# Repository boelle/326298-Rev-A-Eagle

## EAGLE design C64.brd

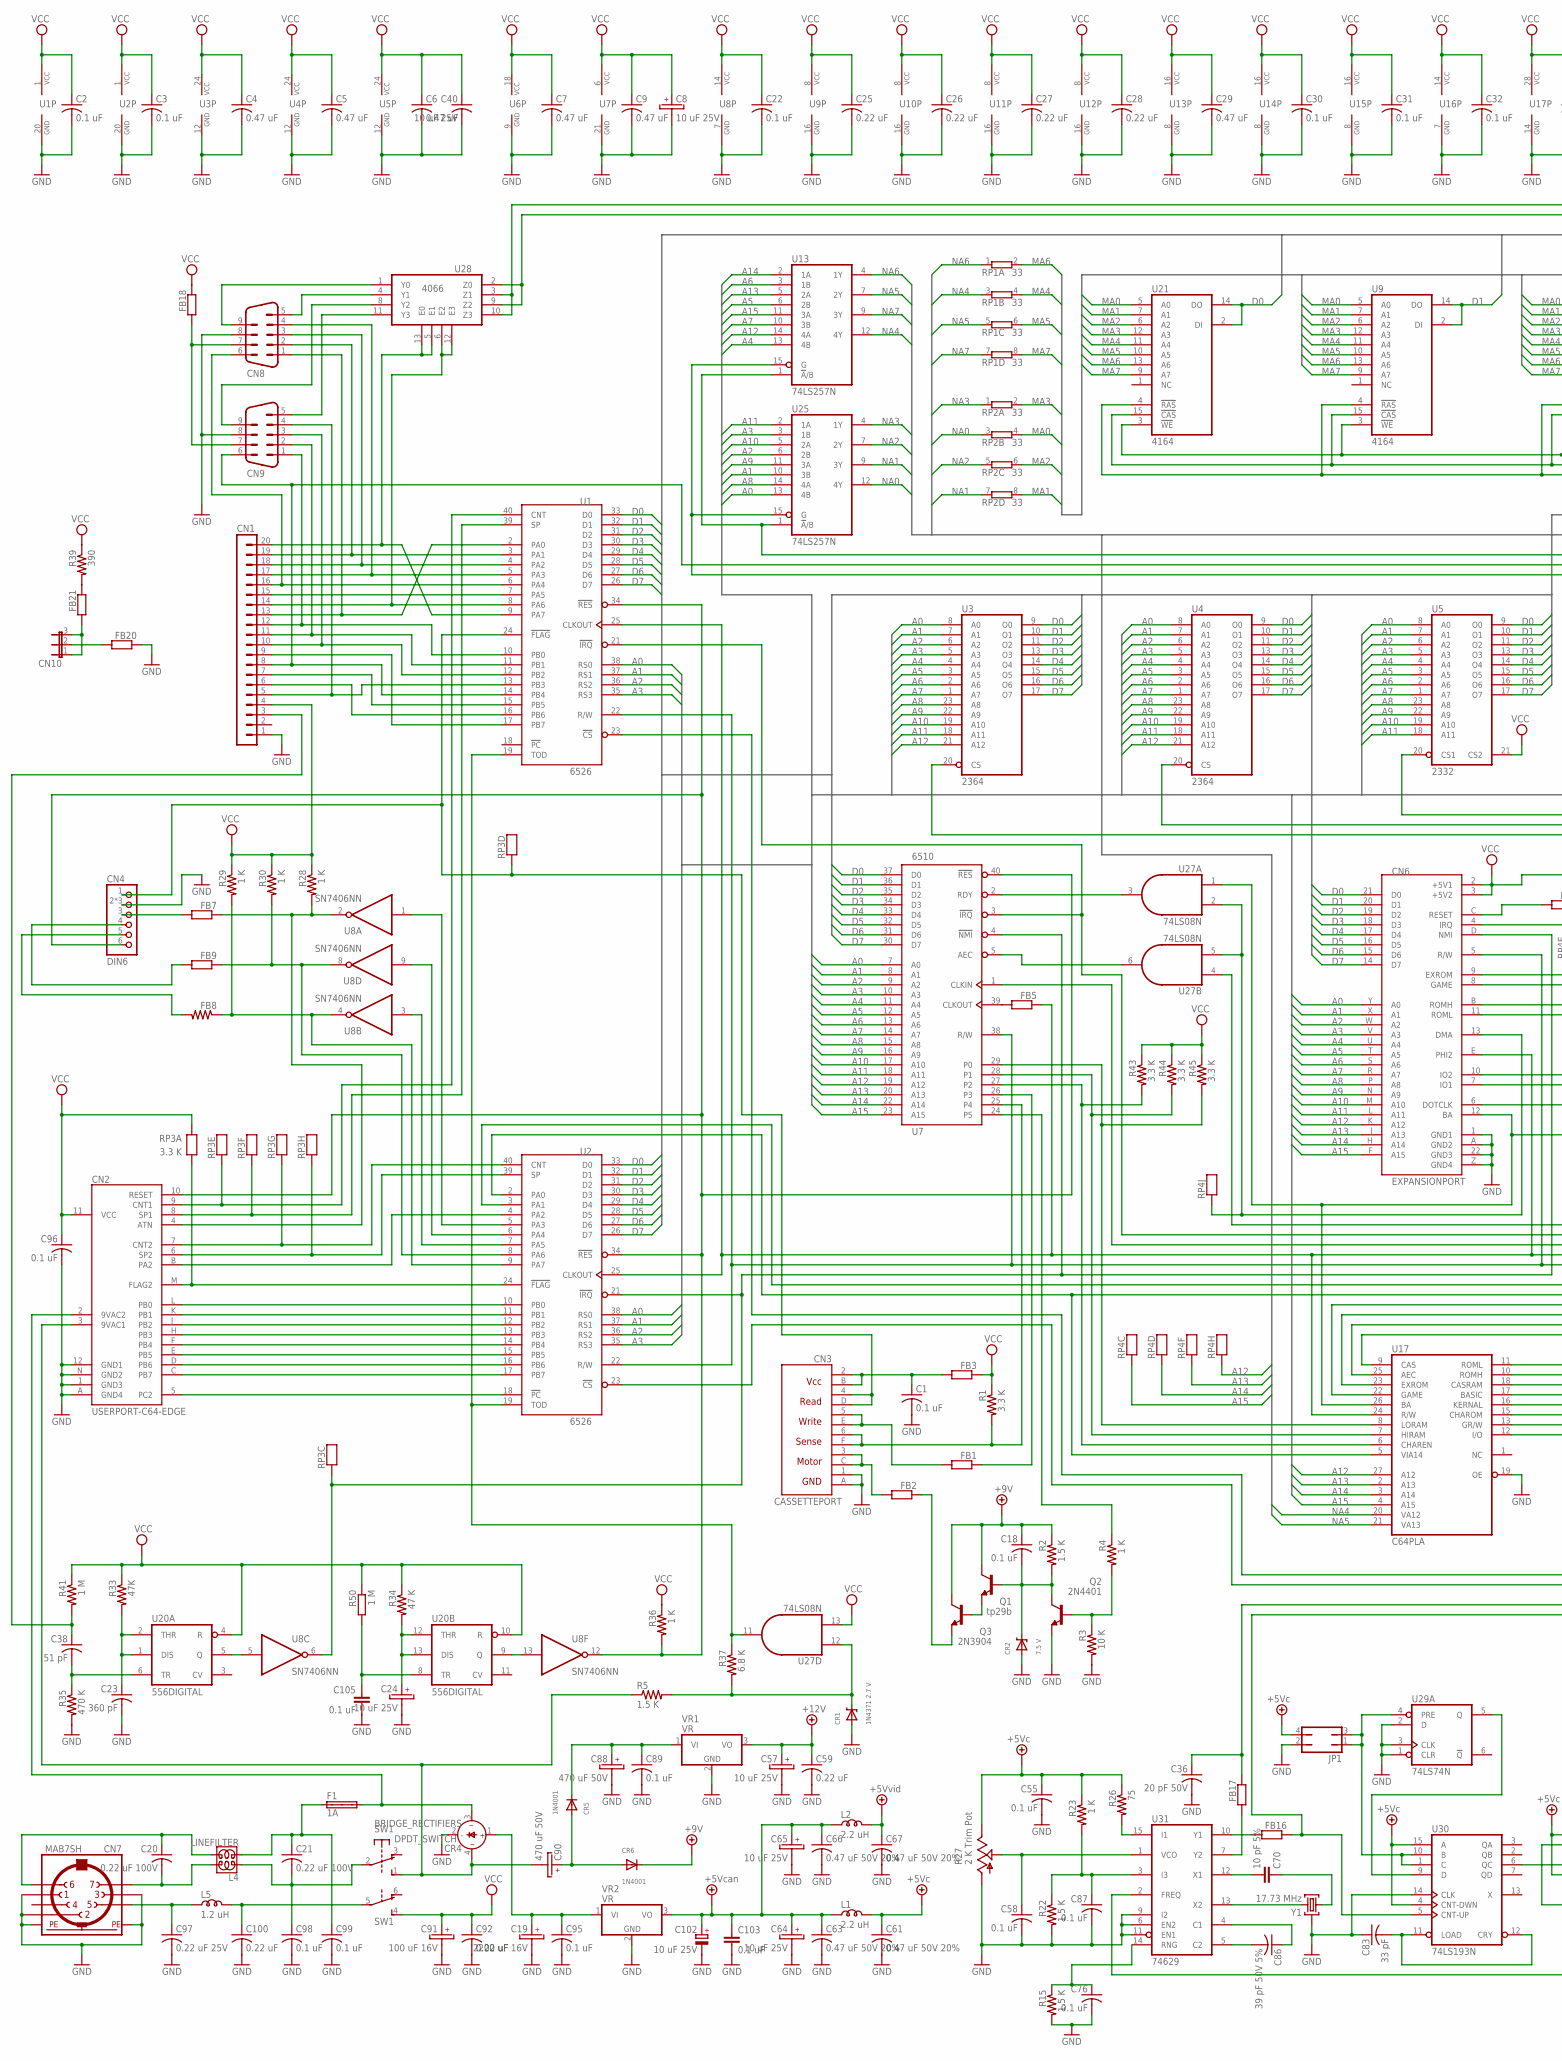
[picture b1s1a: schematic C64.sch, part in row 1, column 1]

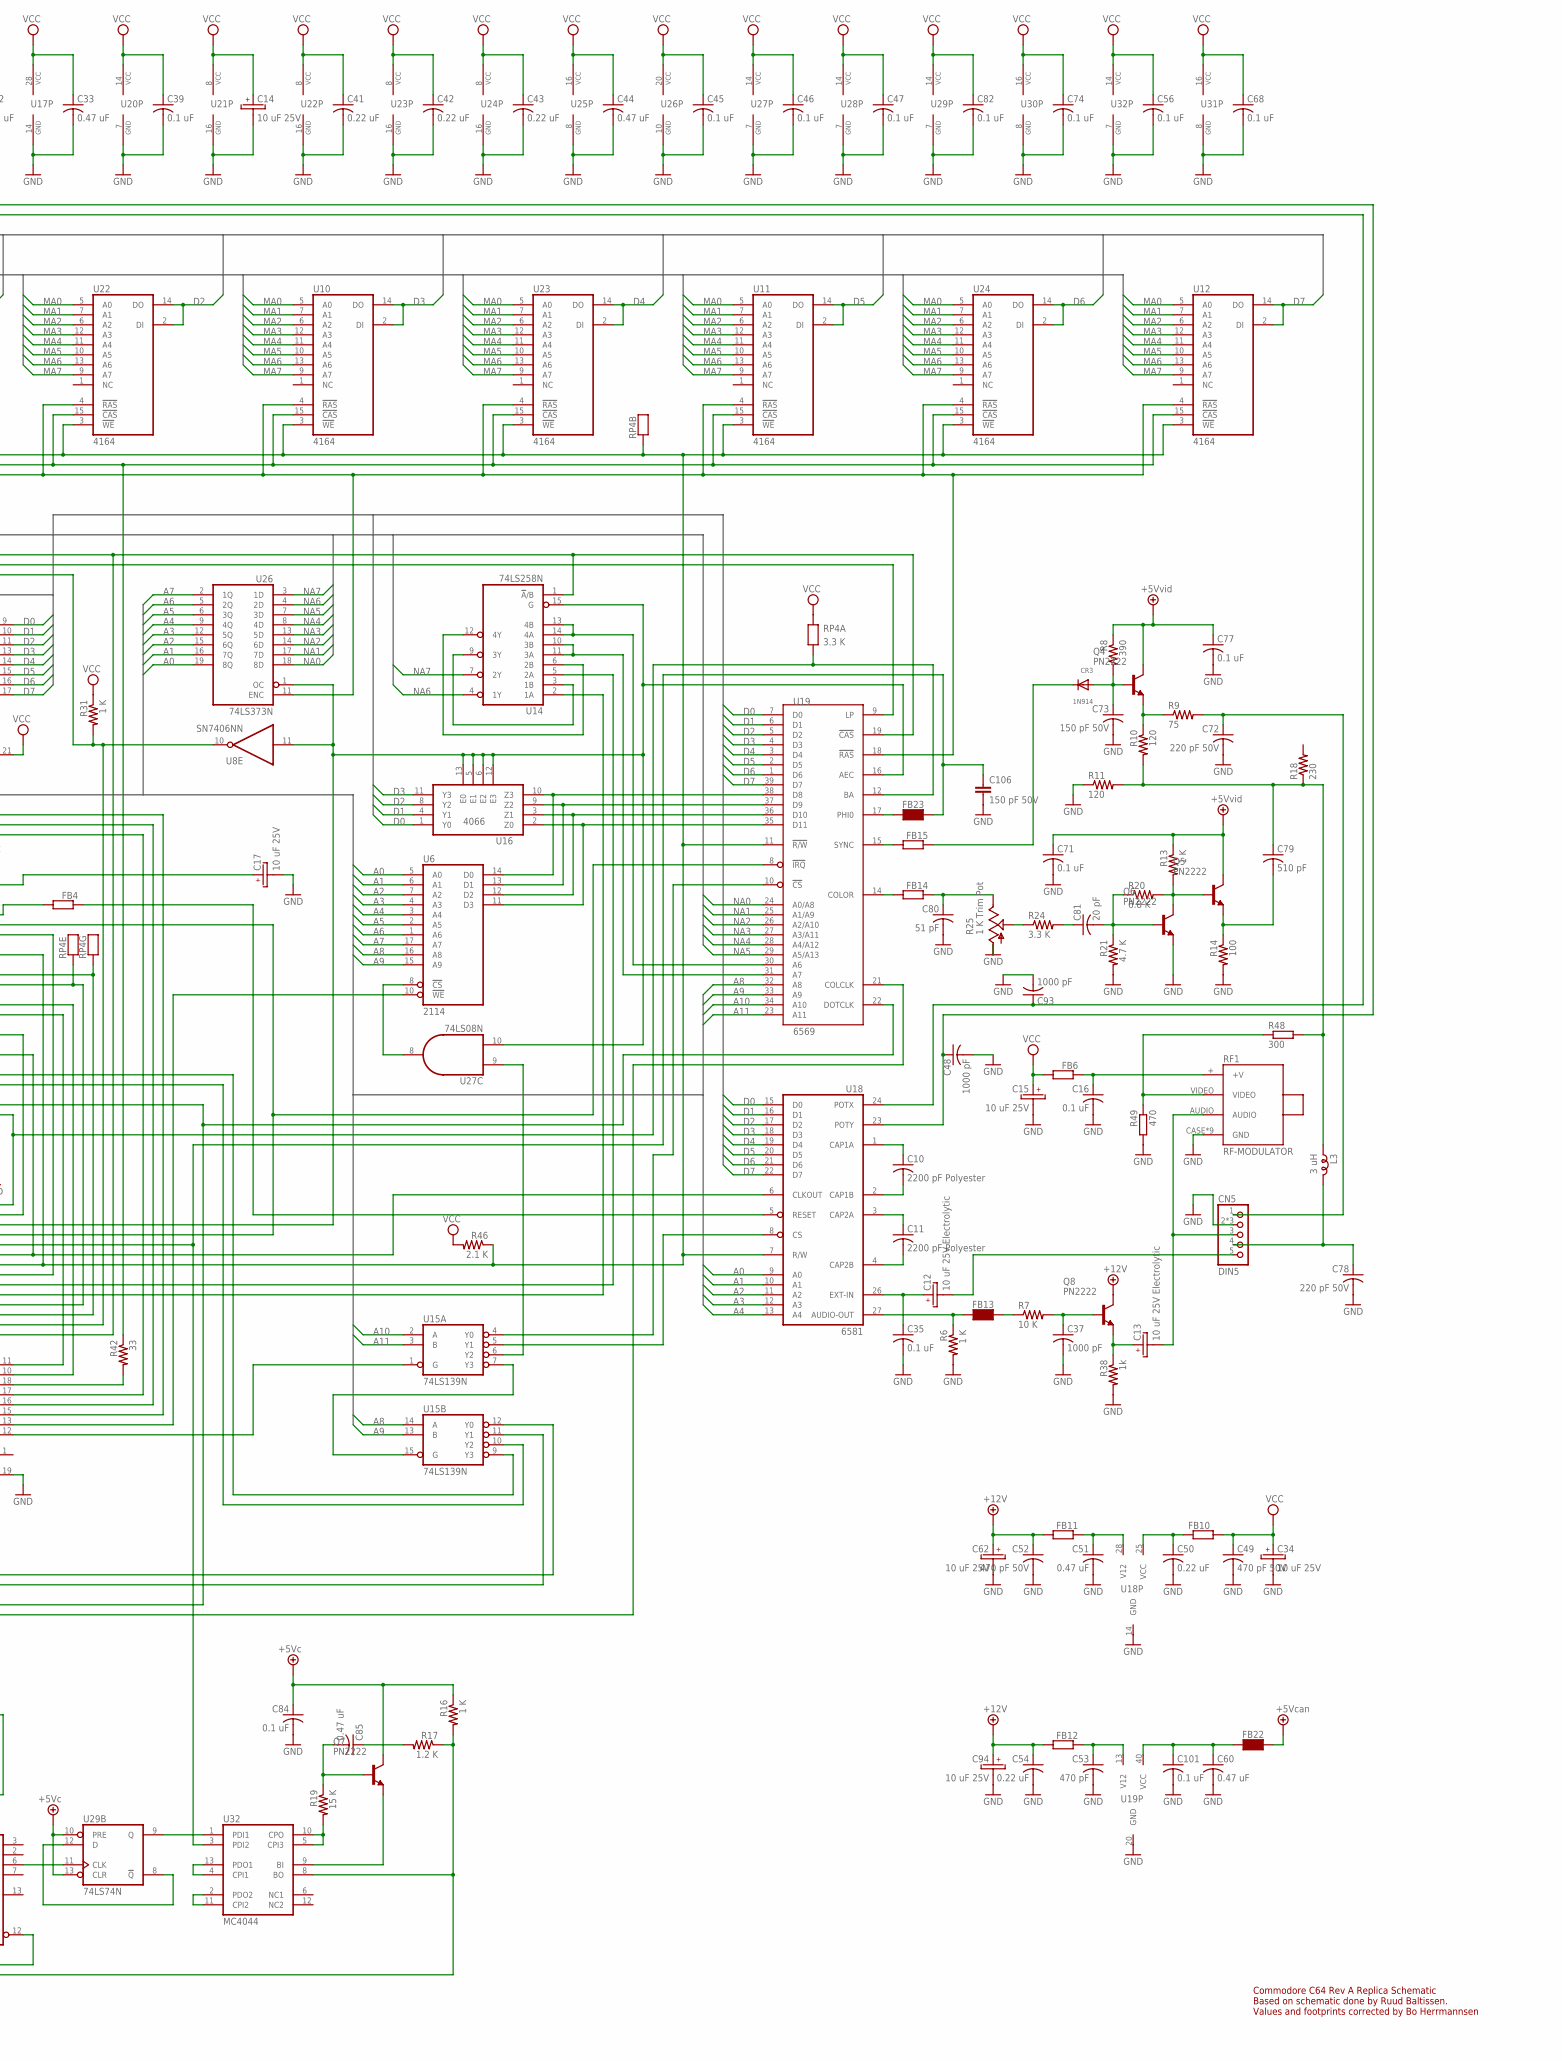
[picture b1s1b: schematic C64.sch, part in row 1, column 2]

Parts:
C1, C2, C3, C16, C18, C30, C31, C32, C35, C45, C46, C47, C89, C95, C96: 0.1 uF; 0307/12
C4, C5, C6, C7, C9, C29, C33, C44, C51: 0.47 uF; 0307/12
C8, C15, C17, C34, C57, C62, C94: 10 uF 25V; E2,5-6E
C10, C11: 2200 pF Polyester; 0307/12
C12, C13: 10 uF 25V Electrolytic; E2,5-6E
C14, C24, C64, C65: 10 uF 25V; CAPACITOR_ELECTROLYTIC_2.5_6
C19: 2200 uF 16V; E37-31.5-17.5-E
C20, C21: 0.22 uF 100V; 0203
C22, C39: 0.1 uF; 12_3_7
C23: 360 pF; 12_3_7
C25, C26, C27, C28, C41, C42, C43: 0.22 uF; 12_3_7
C36: 20 pF 50V; 12_03_07
C37, C48, C93: 1000 pF; 0307/12
C38: 51 pF; 12_3_7
C40: 10 uF 25V; 12_3_7
C49, C52: 470 pF 50V; 0307/12
C50, C54, C59, C92: 0.22 uF; 0307/12
C53: 470 pF; 0307/12
C55, C56, C58, C68, C71, C74, C76, C77, C82, C84, C87: 0.1 uF; 12_03_07
C60, C85: 0.47 uF; 12_03_07
C61, C63, C66, C67: 0.47 uF 50V 20%; 15_4_10
C70: 10 pF 5%; C075-032X103
C72, C78: 220 pF 50V; 12_03_07
C73: 150 pF 50V; 12_03_07
C79: 510 pF; 12_03_07
C80: 51 pF; 12_03_07
C81: 20 pF; 12_03_07
C83: 33 pF; 12_03_07
C86: 39 pF 50V 5%; 12_03_07
C88, C90: 470 uF 50V; E37-31.5-17.5-E
C91: 100 uF 16V; C_E_5-9
C97: 0.22 uF 25V; 0203
C98, C99: 0.1 uF; 0203
C100: 0.22 uF; 0203
C101: 0.1 uF; 6_03_8.5
C102: 10 uF 25V; E3,5-10
C103, C105: 0.1 uF; C075-032X103
C106: 150 pF 50V; C075-032X103
CN1: MA20-1
CN2: USERPORT-C64-EDGE; UPS24EDGE
CN3: CASSETTEPORT
CN4: DIN6
CN5: DIN5
CN6: EXPANSIONPORT
CN7: MAB7SH
CN8, CN9: CONTROL_PORT
CN10: JP2E; JP2
CR1: 1N4371 2.7 V; D_0307/12
CR2: 7.5 V; D_0307/12
CR3: 1N914; D_0307/12
CR4: BRIDGE_RECTIFIERS; DIL4
CR5, CR6: 1N4001; D_0307/12
F1: 1A; SH32
FB1, FB2, FB3, FB4, FB5, FB6, FB10, FB11, FB12, FB14, FB15, FB16, FB17, FB18, FB20, FB21: FB_0307/12R_0307/12; 12_03_07
FB7, FB9: FERRITE_BEAD_12_3_7R_0307/12; 12_3_7
FB8: RESISTOR_12_3_7R_0307/12; 12_3_7
FB13, FB22, FB23: FERRIT; R5
JP1: JP2Q
L1, L2: 2.2 uH; 12_3_7
L3: 3 uH; 12_3_7
L4: LINEFILTER
L5: 1.2 uH; R5
Q1: tp29b; TO220V
Q2: 2N4401; TO92
Q3: 2N3904; TO92
Q4, Q5, Q6, Q7, Q8: PN2222; TO92
R1, R43, R44, R45: 3.3 K; 0307/12
R2, R5: 1.5 K; 0307/12
R3, R7: 10 K; 0307/12
R4, R6: 1 K; 0307/12
R8: 390; 12_03_07
R9, R26: 75; 12_03_07
R10, R11: 120; 12_03_07
R13, R16, R23: 1 K; 12_03_07
R14: 100; 12_03_07
R15, R22: 1.5 K; 12_03_07
R17: 1.2 K; 12_03_07
R18: 230; 12_03_07
R19: 15 K; 12_03_07
R20: 6.8 K; 12_03_07
R21: 4.7 K; 12_03_07
R24: 3.3 K; 12_03_07
R25: 1 K Trim Pot; POT_METER
R27: 2 K Trim Pot; POT_METER
R28, R29, R30, R31, R36: 1 K; 12_3_7
R33: 47K; 12_3_7
R34: 47 K; 12_3_7
R35: 470 K; 12_3_7
R37: 6.8 K; 0307/12
R38: 1k; 12_3_7
R39: 390; 0307/12
R41: 1 M; 0307/12
R42: 33; 12_3_7
R46: 2.1 K; 0307/12
R48: 300; 0204V
R49: 470; 0204V
R50: 1 M; 0204V
RF1: RF-MODULATOR
RP1, RP2: 33; RESISTOR_PACK_4
RP3: 3.3 K; RP8
RP4: 3.3 K; RP9
SW1: DPDT_SWITCH
U1, U2: 6526; DIP40
U3, U4: 2364; DIL24
U5: 2332; DIL24
U6: 2114; DIL18
U7: 6510; DIP40
U8: SN7406NN; DIL14
U9, U10, U11, U12, U21, U22, U23, U24: 4164; DIL16
U13, U25: 74LS257N; DIL16@1
U14: 74LS258N; DIL16@1
U15: 74LS139N; DIL16@1
U16, U28: 4066; DIL14@1
U17: C64PLA; DIL28
U18: 6581; DIL28
U19: 6569; DIP40
U20: 556DIGITAL; DIL14
U26: 74LS373N; DIL20
U27: 74LS08N; DIL14@1
U29: 74LS74N; DIL14@1
U30: 74LS193N; DIL16@1
U31: 74629; DIL16@1
U32: MC4044; DIL14@1
VR1, VR2: VR; TO220V
Y1: 17.73 MHz; HC49TL-H

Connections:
+5V: C63.1, C64.+ (1), C65.+ (1), C66.1, C102.+, C103.1, FB22.2, L1.1, L2.1, VR2.3 (VO)
+5V/1: C67.1, C71.1, C77.1, L2.2, Q4.1 (C), Q5.1 (C), R8.1, R13.1
+5V/2: C55.1, C61.1, C84.1, JP1.4, L1.2, Q7.1 (C), R16.1, R23.1, R26.1, R27.E, U29.10 (PRE), U29.13 (CLR), U30.4 (CNT-DWN), U30.15 (A)
+9V: C18.1, CR6.2 (C), Q1.2 (C), Q3.3 (C), R2.1
+12V: C52.1, C54.1, C57.+ (1), C59.1, C62.+ (1), C94.+ (1), FB11.2, FB12.2, Q8.1 (C), VR1.3 (VO)
A0: CN6.Y (A0), U1.38 (RS0), U2.38 (RS0), U3.8 (A0), U4.8 (A0), U5.8 (A0), U6.5 (A0), U7.7 (A0), U18.9 (A0), U25.13 (4B), U26.19 (8Q)
A1: CN6.X (A1), U1.37 (RS1), U2.37 (RS1), U3.7 (A1), U4.7 (A1), U5.7 (A1), U6.6 (A1), U7.8 (A1), U18.10 (A1), U25.10 (3B), U26.16 (7Q)
A2: CN6.W (A2), U1.36 (RS2), U2.36 (RS2), U3.6 (A2), U4.6 (A2), U5.6 (A2), U6.7 (A2), U7.9 (A2), U18.11 (A2), U25.6 (2B), U26.15 (6Q)
A3: CN6.V (A3), U1.35 (RS3), U2.35 (RS3), U3.5 (A3), U4.5 (A3), U5.5 (A3), U6.4 (A3), U7.10 (A3), U18.12 (A3), U25.3 (1B), U26.12 (5Q)
A4: CN6.U (A4), U3.4 (A4), U4.4 (A4), U5.4 (A4), U6.3 (A4), U7.11 (A4), U13.13 (4B), U18.13 (A4), U26.9 (4Q)
A5: CN6.T (A5), U3.3 (A5), U4.3 (A5), U5.3 (A5), U6.2 (A5), U7.12 (A5), U13.6 (2B), U26.6 (3Q)
A6: CN6.S (A6), U3.2 (A6), U4.2 (A6), U5.2 (A6), U6.1 (A6), U7.13 (A6), U13.3 (1B), U26.5 (2Q)
A7: CN6.R (A7), U3.1 (A7), U4.1 (A7), U5.1 (A7), U6.17 (A7), U7.14 (A7), U13.10 (3B), U26.2 (1Q)
A8: CN6.P (A8), U3.23 (A8), U4.23 (A8), U5.23 (A8), U6.16 (A8), U7.15 (A8), U15.14 (A), U19.32 (A8), U25.14 (4A)
A9: CN6.N (A9), U3.22 (A9), U4.22 (A9), U5.22 (A9), U6.15 (A9), U7.16 (A9), U15.13 (B), U19.33 (A9), U25.11 (3A)
A10: CN6.M (A10), U3.19 (A10), U4.19 (A10), U5.19 (A10), U7.17 (A10), U15.2 (A), U19.34 (A10), U25.5 (2A)
A11: CN6.L (A11), U3.18 (A11), U4.18 (A11), U5.18 (A11), U7.18 (A11), U15.3 (B), U19.23 (A11), U25.2 (1A)
A12: CN6.K (A12), RP4.9 (X), U3.21 (A12), U4.21 (A12), U7.19 (A12), U13.14 (4A), U17.27 (A12)
A13: CN6.J (A13), RP4.7 (X), U7.20 (A13), U13.5 (2A), U17.2 (A13)
A14: CN6.H (A14), RP4.5 (X), U7.22 (A14), U13.2 (1A), U17.3 (A14)
A15: CN6.F (A15), RP4.4 (X), U7.23 (A15), U13.11 (3A), U17.4 (A15)
D0: CN6.21 (D0), U1.33 (D0), U2.33 (D0), U3.9 (O0), U4.9 (O0), U5.9 (O0), U7.37 (D0), U16.1 (Y0), U18.15 (D0), U19.7 (D0), U21.2 (DI), U21.14 (DO)
D1: CN6.20 (D1), U1.32 (D1), U2.32 (D1), U3.10 (O1), U4.10 (O1), U5.10 (O1), U7.36 (D1), U9.2 (DI), U9.14 (DO), U16.4 (Y1), U18.16 (D1), U19.6 (D1)
D2: CN6.19 (D2), U1.31 (D2), U2.31 (D2), U3.11 (O2), U4.11 (O2), U5.11 (O2), U7.35 (D2), U16.8 (Y2), U18.17 (D2), U19.5 (D2), U22.2 (DI), U22.14 (DO)
D3: CN6.18 (D3), U1.30 (D3), U2.30 (D3), U3.13 (O3), U4.13 (O3), U5.13 (O3), U7.34 (D3), U10.2 (DI), U10.14 (DO), U16.11 (Y3), U18.18 (D3), U19.4 (D3)
D4: CN6.17 (D4), U1.29 (D4), U2.29 (D4), U3.14 (O4), U4.14 (O4), U5.14 (O4), U7.33 (D4), U18.19 (D4), U19.3 (D4), U23.2 (DI), U23.14 (DO)
D5: CN6.16 (D5), U1.28 (D5), U2.28 (D5), U3.15 (O5), U4.15 (O5), U5.15 (O5), U7.32 (D5), U11.2 (DI), U11.14 (DO), U18.20 (D5), U19.2 (D5)
D6: CN6.15 (D6), U1.27 (D6), U2.27 (D6), U3.16 (O6), U4.16 (O6), U5.16 (O6), U7.31 (D6), U18.21 (D6), U19.1 (D6), U24.2 (DI), U24.14 (DO)
D7: CN6.14 (D7), U1.26 (D7), U2.26 (D7), U3.17 (O7), U4.17 (O7), U5.17 (O7), U7.30 (D7), U12.2 (DI), U12.14 (DO), U18.22 (D7), U19.39 (D7)
GND: C1.2, C2.2, C3.2, C4.2, C5.2, C6.2, C7.2, C8.- (2), C9.2, C14.- (2), C15.- (2), C16.2, C17.- (2), C19.- (2), C22.2, C23.2, C24.- (2), C25.2, C26.2, C27.2, C28.2, C29.2, C30.2, C31.2, C32.2, C33.2, C34.- (2), C35.2, C36.2, C37.2, C39.2, C40.2, C41.2, C42.2, C43.2, C44.2, C45.2, C46.2, C47.2, C48.2, C49.2, C50.2, C51.2, C52.2, C53.2, C54.2, C55.2, C56.2, C57.- (2), C58.2, C59.2, C60.2, C61.2, C62.- (2), C63.2, C64.- (2), C65.- (2), C66.2, C67.2, C68.2, C71.2, C72.2, C73.2, C74.2, C76.2, C77.2, C78.2, C80.2, C82.2, C83.1, C84.2, C87.2, C88.- (2), C89.2, C91.- (2), C92.2, C93.2, C94.- (2), C95.2, C96.2, C97.2, C98.2, C99.2, C100.2, C101.2, C102.-, C103.2, C105.2, C106.2, CN1.1, CN2.1 (GND3), CN2.12 (GND1), CN2.A (GND4), CN2.N (GND2), CN3.1 (GND1), CN3.A (GND2), CN4.2, CN4.PE (2), CN4.PE@ (2), CN5.2, CN5.PE (2), CN5.PE@ (2), CN6.1 (GND1), CN6.22 (GND3), CN6.A (GND2), CN6.Z (GND4), CN7.1, CN7.2, CN7.3, CN7.PE, CN7.PE@ (PE), CN8.8, CN9.8, CR1.1 (A), CR2.1 (A), CR4.2 (-), FB20.1, JP1.2, Q2.1 (E), Q6.3 (E), R3.2, R6.2, R11.1, R14.2, R15.2, R21.2, R22.2, R25.A, R27.A, R35.2, R38.2, R49.2, RF1.CASE (GND), RF1.P$1 (GND), RF1.P$2 (GND), RF1.P$3 (GND), RF1.P$4 (GND), RF1.P$5 (GND), RF1.P$6 (GND), RF1.P$7 (GND), RF1.P$8 (GND), U1.20 (GND), U2.20 (GND), U3.12 (GND), U4.12 (GND), U5.12 (GND), U6.9 (GND), U7.21 (GND), U8.7 (GND), U9.16 (GND), U10.16 (GND), U11.16 (GND), U12.16 (GND), U13.8 (GND), U14.8 (GND), U15.8 (GND), U16.7 (GND), U17.14 (GND), U17.19 (OE), U18.14 (GND), U19.20 (GND), U20.7 (GND), U21.16 (GND), U22.16 (GND), U23.16 (GND), U24.16 (GND), U25.8 (GND), U26.10 (GND), U27.7 (GND), U28.7 (GND), U29.1 (CLR), U29.2 (D), U29.3 (CLK), U29.7 (GND), U30.8 (GND), U30.14 (CLK), U31.6 (EN2), U31.8 (GND), U31.9 (I2), U31.11 (EN1), U32.7 (GND), VR1.2 (GND), VR2.2 (GND), Y1.3
IRQ: CN6.4 (IRQ), U1.21 (!IRQ!), U7.3 (!IRQ!), U19.8 (!IRQ!)
MA0: RP2.4 (2), U9.5 (A0), U10.5 (A0), U11.5 (A0), U12.5 (A0), U21.5 (A0), U22.5 (A0), U23.5 (A0), U24.5 (A0)
MA1: RP2.8 (2), U9.7 (A1), U10.7 (A1), U11.7 (A1), U12.7 (A1), U21.7 (A1), U22.7 (A1), U23.7 (A1), U24.7 (A1)
MA2: RP2.6 (2), U9.6 (A2), U10.6 (A2), U11.6 (A2), U12.6 (A2), U21.6 (A2), U22.6 (A2), U23.6 (A2), U24.6 (A2)
MA3: RP2.2, U9.12 (A3), U10.12 (A3), U11.12 (A3), U12.12 (A3), U21.12 (A3), U22.12 (A3), U23.12 (A3), U24.12 (A3)
MA4: RP1.4 (2), U9.11 (A4), U10.11 (A4), U11.11 (A4), U12.11 (A4), U21.11 (A4), U22.11 (A4), U23.11 (A4), U24.11 (A4)
MA5: RP1.6 (2), U9.10 (A5), U10.10 (A5), U11.10 (A5), U12.10 (A5), U21.10 (A5), U22.10 (A5), U23.10 (A5), U24.10 (A5)
MA6: RP1.2, U9.13 (A6), U10.13 (A6), U11.13 (A6), U12.13 (A6), U21.13 (A6), U22.13 (A6), U23.13 (A6), U24.13 (A6)
MA7: RP1.8 (2), U9.9 (A7), U10.9 (A7), U11.9 (A7), U12.9 (A7), U21.9 (A7), U22.9 (A7), U23.9 (A7), U24.9 (A7)
unnamed: C12.+ (1), C35.1, U18.26 (EXT-IN)
unnamed: FB13.1, R6.1, U18.27 (AUDIO-OUT)
unnamed: FB13.2, R7.1
unnamed: C37.1, Q8.2 (B), R7.2
unnamed: C13.+ (1), Q8.3 (E), R38.1
unnamed: C10.2, U18.2 (CAP1B)
unnamed: C11.2, U18.4 (CAP2B)
unnamed: C10.1, U18.1 (CAP1A)
unnamed: C11.1, U18.3 (CAP2A)
unnamed: C13.- (2), CN5.3, RF1.AUDIO
unnamed: C12.- (2), CN5.5
unnamed: C50.1, FB10.1, U18.25 (VCC)
unnamed: C16.1, FB6.1, RF1.+ (+V)
unnamed: C51.1, FB11.1, U18.28 (V12)
unnamed: C80.1, FB14.1, R25.E
unnamed: FB14.2, U19.14 (COLOR)
unnamed: C97.1, CN7.5, L5.1
unnamed: C100.1, L5.2, SW1.5
unnamed: C20.2, CN7.7, L4.4
unnamed: C20.1, CN7.6, L4.3
unnamed: C21.1, C99.1, F1.1A, L4.2
unnamed: C21.2, C98.1, L4.1, SW1.2
unnamed: CN2.2 (9VAC2), CR4.3 (AC1), F1.2A
unnamed: C90.- (2), CN2.3 (9VAC1), CR4.4 (AC2), R5.1, SW1.1 (S)
unnamed: C19.+ (1), C95.1, CR4.1 (+), VR2.1 (VI)
unnamed: C90.+ (1), CR5.1 (A), CR6.1 (A)
unnamed: C88.+ (1), C89.1, CR5.2 (C), VR1.1 (VI)
unnamed: R24.1, R25.S
unnamed: C81.1, R24.2
unnamed: C81.2, Q6.2 (B), R20.1, R21.1
unnamed: Q5.2 (B), Q6.1 (C), R13.2, R20.2
unnamed: C79.2, Q5.3 (E), R14.1
unnamed: C79.1, L3.1, R10.2, R11.2, R18.1, R48.2
unnamed: C60.1, C101.1, FB22.1, U19.40 (VCC)
unnamed: C53.1, FB12.1, U19.13 (V12)
unnamed: C73.1, CR3.1 (A), Q4.2 (B), R8.2
unnamed: CR3.2 (C), FB15.1
unnamed: Q4.3 (E), R9.1, R10.1
unnamed: C72.1, CN5.1, R9.2
unnamed: FB15.2, U19.15 (SYNC)
unnamed: C78.1, CN5.4, L3.2
unnamed: U14.10 (3B), U14.11 (3A), U19.31 (A7)
unnamed: R48.1, R49.1, RF1.VIDEO
unnamed: U14.13 (4B), U14.14 (4A), U19.30 (A6)
unnamed: U14.3 (1B), U14.9 (3Y)
unnamed: U14.6 (2B), U14.12 (4Y)
unnamed: U6.14 (D0), U16.10 (Z3), U19.38 (D8)
unnamed: U6.13 (D1), U16.9 (Z2), U19.37 (D9)
unnamed: U6.12 (D2), U16.3 (Z1), U19.36 (D10)
unnamed: U6.11 (D3), U16.2 (Z0), U19.35 (D11)
unnamed: R42.2, U17.18 (CASRAM)
unnamed: U8.11 (I), U14.15 (G), U16.5 (E1), U16.6 (E2), U16.12 (E3), U16.13 (E0), U19.16 (AEC), U26.1 (OC), U27.4 (I0), U27.10 (I1)
unnamed: U13.1 (!A!/B), U14.1 (!A!/B), U17.9 (CAS), U19.19 (!CAS!), U25.1 (!A!/B)
unnamed: R42.1, U9.15 (!CAS), U10.15 (!CAS), U11.15 (!CAS), U12.15 (!CAS), U21.15 (!CAS), U22.15 (!CAS), U23.15 (!CAS), U24.15 (!CAS)
unnamed: U9.4 (!RAS), U10.4 (!RAS), U11.4 (!RAS), U12.4 (!RAS), U19.18 (!RAS!), U21.4 (!RAS), U22.4 (!RAS), U23.4 (!RAS), U24.4 (!RAS), U26.11 (ENC)
unnamed: U6.8 (!CS), U27.8 (O)
unnamed: U8.13 (I), U20.9 (Q)
unnamed: C24.+ (1), R34.2, U20.12 (THR), U20.13 (DIS)
unnamed: C105.1, R50.2, U20.8 (TR)
unnamed: U8.5 (I), U20.5 (Q)
unnamed: C23.1, R33.2, U20.1 (DIS), U20.2 (THR)
unnamed: C38.2, R35.1, U20.6 (TR)
unnamed: C38.1, CN1.3, R41.2
unnamed: R26.2, U31.15 (I1)
unnamed: C58.1, R27.S, U31.1 (VCO)
unnamed: FB16.2, U31.10 (Y1)
unnamed: U31.13 (X2), Y1.2
unnamed: C70.2, U31.12 (X1)
unnamed: C70.1, Y1.1
unnamed: FB16.1, U19.21 (COLCLK), U30.5 (CNT-UP)
unnamed: C83.2, U30.11 (LOAD), U30.12 (CRY)
unnamed: JP1.1, JP1.3, U29.4 (PRE), U30.1 (C), U30.10 (B)
unnamed: U29.5 (Q), U30.9 (D)
unnamed: R16.2, R17.1, U31.2 (FREQ), U32.8 (BO)
unnamed: U29.11 (CLK), U30.6 (QC)
unnamed: U29.8 (!Q), U29.12 (D)
unnamed: U32.2 (PDO2), U32.11 (CPI2)
unnamed: U32.4 (CPI1), U32.13 (PDO1)
unnamed: C87.1, R22.1, R23.2, U31.3 (I3)
unnamed: C86.1, U31.4 (C1)
unnamed: C86.2, U31.5 (C2)
unnamed: FB17.2, U31.7 (Y2)
unnamed: U29.9 (Q), U32.1 (PDI1)
unnamed: CN3.5 (WRITE1), CN3.E (WRITE2), FB1.2
unnamed: R19.2, U32.5 (CPI3), U32.10 (CPO)
unnamed: C85.1, R17.2
unnamed: C36.1, CN6.6 (DOTCLK), FB17.1, U19.22 (DOTCLK)
unnamed: C85.2, Q7.2 (B), R19.1
unnamed: R31.2, U8.10 (O), U13.15 (G), U17.25 (AEC), U25.15 (G)
unnamed: Q7.3 (E), U32.9 (BI)
unnamed: CN1.19, CN8.2, U1.3 (PA1)
unnamed: CN1.18, CN8.3, U1.4 (PA2)
unnamed: CN1.17, CN8.4, U1.5 (PA3)
unnamed: CN1.16, CN8.6, U1.6 (PA4)
unnamed: CN1.15, U1.7 (PA5)
unnamed: CN1.14, U1.8 (PA6), U28.6 (E2), U28.12 (E3)
unnamed: CN1.20, U1.9 (PA7), U28.5 (E1), U28.13 (E0)
unnamed: CN1.13, CN8.1, U1.2 (PA0)
unnamed: CN1.12, CN9.1, U1.10 (PB0)
unnamed: CN1.11, CN9.2, U1.11 (PB1)
unnamed: CN1.10, CN9.3, U1.12 (PB2)
unnamed: CN1.9, U1.17 (PB7)
unnamed: CN1.8, CN9.6, U1.14 (PB4), U19.9 (LP)
unnamed: CN1.7, U1.15 (PB5)
unnamed: CN1.5, CN9.4, U1.13 (PB3)
unnamed: CN1.6, U1.16 (PB6)
unnamed: CN8.9, U28.1 (Y0)
unnamed: CN8.5, U28.4 (Y1)
unnamed: CN8.7, CN9.7, FB18.2
unnamed: CN9.9, U28.8 (Y2)
unnamed: CN9.5, U28.11 (Y3)
unnamed: C93.1, U18.24 (POTX), U28.2 (Z0), U28.9 (Z2)
unnamed: C48.1, U18.23 (POTY), U28.3 (Z1), U28.10 (Z3)
unnamed: CN4.3, FB7.2
unnamed: CN4.4, FB9.2
unnamed: CN4.5, FB8.2
unnamed: FB8.1, R29.2, U2.9 (PA7), U8.4 (O)
unnamed: FB9.1, R30.2, U2.8 (PA6), U8.8 (O)
unnamed: CN2.4 (ATN), FB7.1, R28.2, U8.2 (O)
unnamed: CN2.5 (PC2), U2.18 (!PC!)
unnamed: CN2.C (PB7), U2.17 (PB7)
unnamed: CN2.D (PB6), U2.16 (PB6)
unnamed: CN2.E (PB5), U2.15 (PB5)
unnamed: CN2.F (PB4), U2.14 (PB4)
unnamed: CN2.H (PB3), U2.13 (PB3)
unnamed: CN2.J (PB2), U2.12 (PB2)
unnamed: CN2.K (PB1), U2.11 (PB1)
unnamed: CN2.L (PB0), U2.10 (PB0)
unnamed: CN2.M (FLAG2), RP3.2, U2.24 (!FLAG!)
unnamed: U2.7 (PA5), U8.3 (I)
unnamed: U2.6 (PA4), U8.9 (I)
unnamed: U2.5 (PA3), U8.1 (I)
unnamed: CN3.3 (MOTOR1), CN3.C (MOTOR2), FB2.2
unnamed: CN2.9 (CNT1), RP3.5 (X), U1.40 (CNT)
unnamed: U2.2 (PA0), U14.2 (1A), U17.5 (VIA14)
unnamed: U2.3 (PA1), U14.5 (2A)
unnamed: CN2.B (PA2), U2.4 (PA2)
unnamed: CN2.6 (SP2), RP3.8 (X), U2.39 (SP)
unnamed: CN2.7 (CNT2), RP3.7 (X), U2.40 (CNT)
unnamed: CN2.8 (SP1), RP3.6 (X), U1.39 (SP)
unnamed: FB5.2, U7.39 (CLKOUT)
unnamed: C76.1, R15.1, U31.14 (RNG)
unnamed: U3.20 (CS), U17.17 (BASIC)
unnamed: CR1.2 (C), R5.2, R37.2, U27.12 (I0)
unnamed: R37.1, U1.19 (TOD), U2.19 (TOD), U27.11 (O)
unnamed: CN10.1, CN10.3, FB21.2
unnamed: CN10.2, FB20.2
unnamed: FB4.1, U18.5 (RESET)
unnamed: FB21.1, R39.2
unnamed: U4.20 (CS), U17.16 (KERNAL)
unnamed: CN6.C (RESET), FB4.2
unnamed: CN6.12 (BA), RP4.2, U17.26 (BA), U19.12 (BA), U27.1 (I0)
unnamed: CN6.11 (ROML), U17.11 (ROML)
unnamed: CN6.B (ROMH), U17.10 (ROMH)
unnamed: CN6.9 (EXROM), RP4.8 (X), U17.23 (EXROM)
unnamed: CN6.8 (GAME), RP4.6 (X), U17.22 (GAME)
unnamed: FB23.2, U19.17 (PHI0)
unnamed: U15.4 (Y0), U19.10 (!CS!)
unnamed: R45.2, U7.29 (P0), U17.8 (LORAM)
unnamed: R44.2, U7.28 (P1), U17.7 (HIRAM)
unnamed: R43.2, U7.27 (P2), U17.6 (CHAREN)
unnamed: U7.2 (RDY), U27.3 (O)
unnamed: U7.5 (AEC), U27.6 (O)
unnamed: CN6.13 (DMA), RP4.10 (X), U27.2 (I1), U27.5 (I1)
unnamed: U5.20 (CS1), U17.15 (CHAROM)
unnamed: CN3.4 (READ1), CN3.D (READ2), CN4.1, RP3.4 (X), U1.24 (!FLAG!)
unnamed: CN3.6 (SENSE1), CN3.F (SENSE2), R1.2, U7.25 (P4)
unnamed: C1.1, CN3.2 (VCC1), CN3.B (VCC2), FB3.2
unnamed: FB1.1, U7.26 (P3)
unnamed: Q2.2 (B), R3.1, R4.2
unnamed: Q1.3 (E), Q3.2 (B)
unnamed: C18.2, CR2.2 (C), Q1.1 (B), Q2.3 (C), R2.2
unnamed: FB2.1, Q3.1 (E)
unnamed: R4.1, U7.24 (P5)
unnamed: U1.23 (!CS!), U15.12 (Y0)
unnamed: U2.23 (!CS!), U15.11 (Y1)
unnamed: U6.10 (!WE), U17.13 (GR/W)
unnamed: U15.1 (G), U17.12 (I/O)
unnamed: U15.7 (Y3), U15.15 (G)
unnamed: CN6.7 (IO1), U15.10 (Y2)
unnamed: CN6.10 (IO2), U15.9 (Y3)
unnamed: U15.5 (Y1), U18.8 (CS)
unnamed: U15.6 (Y2), U27.9 (I0)
NA0: RP2.3 (1), U19.24 (A0/A8), U25.12 (4Y), U26.18 (8D)
NA1: RP2.7 (1), U19.25 (A1/A9), U25.9 (3Y), U26.17 (7D)
NA2: RP2.5 (1), U19.26 (A2/A10), U25.7 (2Y), U26.14 (6D)
NA3: RP2.1, U19.27 (A3/A11), U25.4 (1Y), U26.13 (5D)
NA4: RP1.3 (1), U13.12 (4Y), U17.20 (VA12), U19.28 (A4/A12), U26.8 (4D)
NA5: RP1.5 (1), U13.7 (2Y), U17.21 (VA13), U19.29 (A5/A13), U26.7 (3D)
NA6: RP1.1, U13.4 (1Y), U14.4 (1Y), U26.4 (2D)
NA7: RP1.7 (1), U13.9 (3Y), U14.7 (2Y), U26.3 (1D)
NMI: CN6.D (NMI), RP3.3 (X), U2.21 (!IRQ!), U7.4 (!NMI!), U8.6 (O)
PHI0: C106.1, FB23.1, U7.1 (CLKIN), U32.3 (PDI2)
PHI2: CN6.E (PHI2), FB5.1, U1.25 (CLKOUT), U2.25 (CLKOUT), U17.24 (R/W), U18.6 (CLKOUT)
RES: CN2.10 (RESET), CN4.6, R36.2, U1.34 (!RES!), U2.34 (!RES!), U7.40 (!RES!), U8.12 (O)
RW: CN6.5 (R/W), R46.1, RP4.3 (X), U1.22 (R/W), U2.22 (R/W), U7.38 (R/W), U9.3 (!WE), U10.3 (!WE), U11.3 (!WE), U12.3 (!WE), U18.7 (R/W), U19.11 (!R/W!), U21.3 (!WE), U22.3 (!WE), U23.3 (!WE), U24.3 (!WE)
VCC: C2.1, C3.1, C4.1, C5.1, C6.1, C7.1, C8.+ (1), C9.1, C14.+ (1), C15.+ (1), C17.+ (1), C22.1, C25.1, C26.1, C27.1, C28.1, C29.1, C30.1, C31.1, C32.1, C33.1, C34.+ (1), C39.1, C40.1, C41.1, C42.1, C43.1, C44.1, C45.1, C46.1, C47.1, C49.1, C56.1, C68.1, C74.1, C82.1, C91.+ (1), C92.1, C96.1, CN1.4, CN2.11 (VCC), CN6.2 (+5V1), CN6.3 (+5V2), FB3.1, FB6.2, FB10.2, FB18.1, R1.1, R28.1, R29.1, R30.1, R31.1, R33.1, R34.1, R36.1, R39.1, R41.1, R43.1, R44.1, R45.1, R46.2, R50.1, RP3.1, RP4.1, SW1.4 (S), U1.1 (VCC), U2.1 (VCC), U3.24 (VCC), U4.24 (VCC), U5.21 (CS2), U5.24 (VCC), U6.18 (VCC), U7.6 (VCC), U8.14 (VCC), U9.8 (VCC), U10.8 (VCC), U11.8 (VCC), U12.8 (VCC), U13.16 (VCC), U14.16 (VCC), U15.16 (VCC), U16.14 (VCC), U17.28 (VCC), U20.4 (R), U20.10 (R), U20.14 (VCC), U21.8 (VCC), U22.8 (VCC), U23.8 (VCC), U24.8 (VCC), U25.16 (VCC), U26.20 (VCC), U27.13 (I1), U27.14 (VCC), U28.14 (VCC), U29.14 (VCC), U30.16 (VCC), U31.16 (VCC), U32.14 (VCC)

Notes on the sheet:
Commodore C64 Rev A Replica Schematic Based on schematic done by Ruud Baltissen. Values and footprints corrected by Bo Herrmannsen

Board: 2 copper layers, 243 parts (0 on the bottom side), 236 nets, no tracks yet.

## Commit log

2018-02-24 initial push after split up
